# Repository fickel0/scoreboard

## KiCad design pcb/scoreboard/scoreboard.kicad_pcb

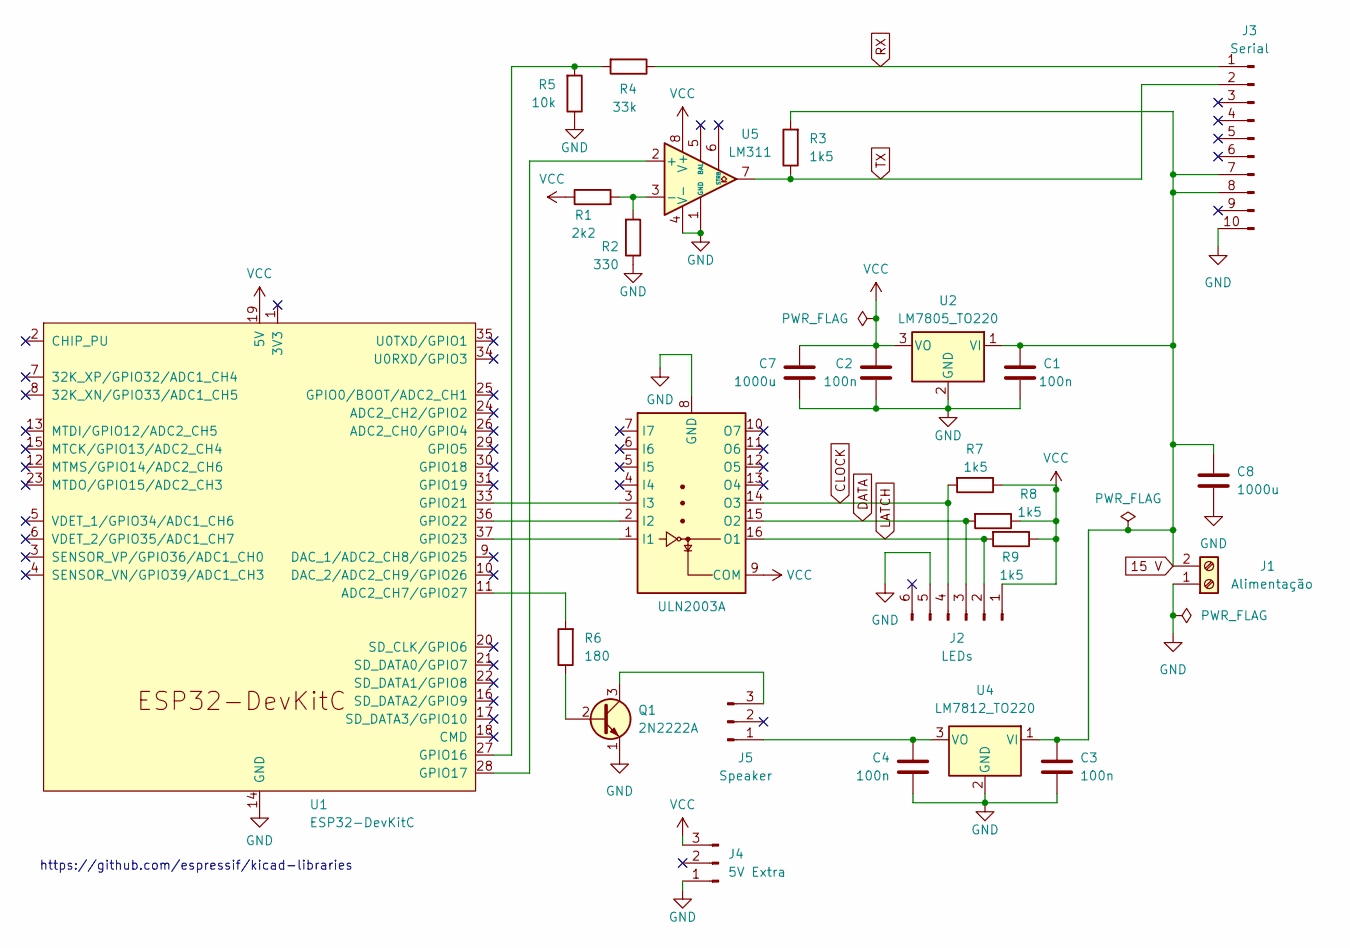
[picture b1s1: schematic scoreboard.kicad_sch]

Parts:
C1, C2, C3, C4: 100n; C_Disc_D5.0mm_W2.5mm_P2.50mm
C7, C8: 1000u; C_Radial_D8.0mm_H11.5mm_P3.50mm
J1: Alimentação; TerminalBlock_Altech_AK300-2_P5.00mm
J2: LEDs; PinHeader_1x06_P2.54mm_Vertical
J3: Serial; PinHeader_2x05_P2.54mm_Vertical
J4: 5V Extra; PinHeader_1x03_P2.54mm_Vertical
J5: Speaker; PinHeader_1x03_P2.54mm_Vertical
Q1: 2N2222A; TO-92_EBC
R1: 2k2; R_Axial_DIN0204_L3.6mm_D1.6mm_P7.62mm_Horizontal
R2: 330; R_Axial_DIN0204_L3.6mm_D1.6mm_P7.62mm_Horizontal
R3, R7: 1k5; R_Axial_DIN0204_L3.6mm_D1.6mm_P7.62mm_Horizontal
R4: 33k; R_Axial_DIN0204_L3.6mm_D1.6mm_P7.62mm_Horizontal
R5: 10k; R_Axial_DIN0204_L3.6mm_D1.6mm_P7.62mm_Horizontal
R6: 180; R_Axial_DIN0204_L3.6mm_D1.6mm_P10.16mm_Horizontal
R8, R9: 1k5; R_Axial_DIN0204_L3.6mm_D1.6mm_P5.08mm_Horizontal
U1: ESP32-DevKitC
U2: LM7805_TO220; TO-220-3_Vertical
U3: ULN2003A; DIP-16_W7.62mm_LongPads
U4: LM7812_TO220; TO-220-3_Vertical
U5: LM311; DIP-8_W7.62mm_LongPads

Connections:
15 V: C1.1, C3.1, C8.1, J1.2, J3.7, J3.8, R3.2, U2.1 (VI), U4.1 (VI)
CLOCK: J2.4, R7.2, U3.14 (O3)
DATA: J2.3, R8.2, U3.15 (O2)
GND: C1.2, C2.2, C3.2, C4.2, C7.2, C8.2, J1.1, J2.5, J3.10, J4.1, Q1.1 (E), R2.1, R5.1, U1.14 (GND), U1.32 (GND), U1.38 (GND), U2.2 (GND), U3.8 (GND), U4.2 (GND), U5.1 (GND), U5.4 (V-)
LATCH: J2.2, R9.2, U3.16 (O1)
unnamed: C4.1, J5.1, U4.3 (VO)
unnamed: J5.3, Q1.3 (C)
unnamed: Q1.2 (B), R6.1
unnamed: R6.2, U1.11 (ADC2_CH7/GPIO27)
unnamed: R4.2, R5.2, U1.27 (GPIO16)
unnamed: U1.28 (GPIO17), U5.2 (+)
unnamed: U1.33 (GPIO21), U3.3 (I3)
unnamed: U1.36 (GPIO22), U3.2 (I2)
unnamed: U1.37 (GPIO23), U3.1 (I1)
unnamed: R1.2, R2.2, U5.3 (-)
RX: J3.1, R4.1
TX: J3.2, R3.1, U5.7
VCC: C2.1, C7.1, J2.1, J4.3, R1.1, R7.1, R8.1, R9.1, U1.19 (5V), U2.3 (VO), U3.9 (COM), U5.8 (V+)

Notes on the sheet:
https://github.com/espressif/kicad-libraries

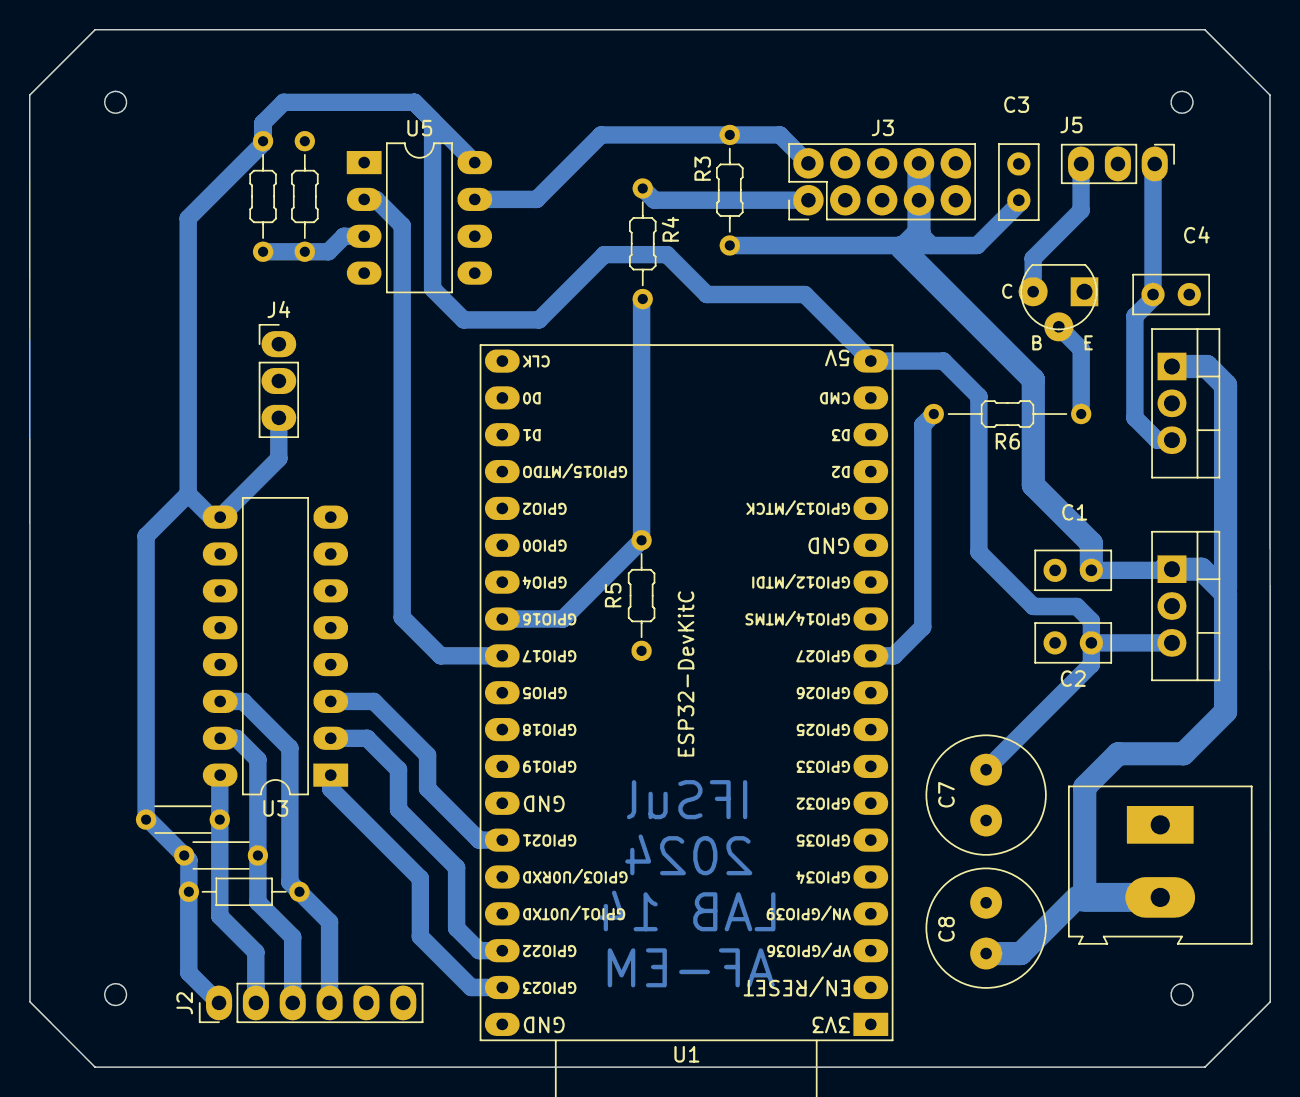
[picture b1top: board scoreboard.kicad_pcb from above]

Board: 2 copper layers, 85.5 x 71.5 mm, 26 parts (0 on the bottom side), 18 nets.

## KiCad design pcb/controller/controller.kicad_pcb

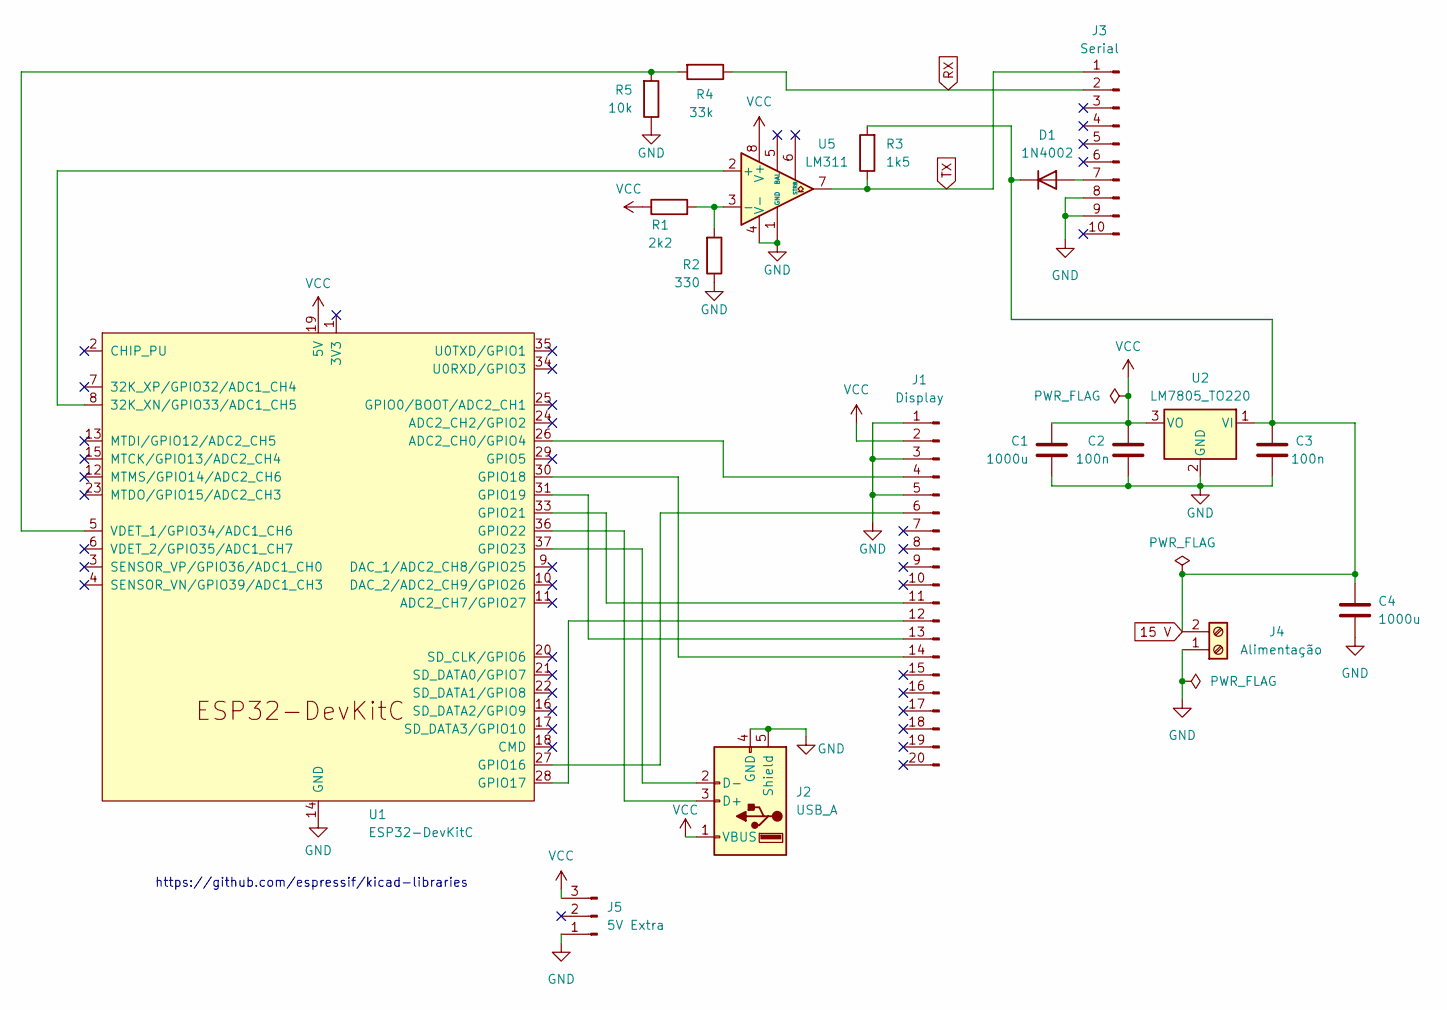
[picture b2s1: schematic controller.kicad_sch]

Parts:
C1, C4: 1000u; C_Radial_D8.0mm_H11.5mm_P3.50mm
C2, C3: 100n; C_Disc_D5.0mm_W2.5mm_P2.50mm
D1: 1N4002; D_DO-41_SOD81_P10.16mm_Horizontal
J1: Display; PinHeader_2x10_P2.54mm_Vertical
J2: USB_A; USB_A_Wuerth_614004134726_Horizontal
J3: Serial; PinHeader_2x05_P2.54mm_Vertical
J4: Alimentação; TerminalBlock_Altech_AK300-2_P5.00mm
J5: 5V Extra; PinHeader_1x03_P2.54mm_Vertical
R1: 2k2; R_Axial_DIN0204_L3.6mm_D1.6mm_P7.62mm_Horizontal
R2: 330; R_Axial_DIN0204_L3.6mm_D1.6mm_P7.62mm_Horizontal
R3: 1k5; R_Axial_DIN0204_L3.6mm_D1.6mm_P7.62mm_Horizontal
R4: 33k; R_Axial_DIN0204_L3.6mm_D1.6mm_P7.62mm_Horizontal
R5: 10k; R_Axial_DIN0204_L3.6mm_D1.6mm_P7.62mm_Horizontal
U1: ESP32-DevKitC
U2: LM7805_TO220; TO-220-3_Vertical
U5: LM311; DIP-8_W7.62mm_LongPads

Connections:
15 V: C3.1, C4.1, D1.1 (K), J4.2, R3.2, U2.1 (VI)
GND: C1.2, C2.2, C3.2, C4.2, J1.1, J1.3, J1.5, J2.4 (GND), J2.5 (Shield), J3.8, J3.9, J4.1, J5.1, R2.1, R5.1, U1.14 (GND), U1.32 (GND), U1.38 (GND), U2.2 (GND), U5.1 (GND), U5.4 (V-)
unnamed: D1.2 (A), J3.7
unnamed: J1.4, U1.26 (ADC2_CH0/GPIO4)
unnamed: J1.6, U1.27 (GPIO16)
unnamed: J1.11, U1.33 (GPIO21)
unnamed: J1.12, U1.28 (GPIO17)
unnamed: J1.13, U1.31 (GPIO19)
unnamed: J1.14, U1.30 (GPIO18)
unnamed: J2.3 (D+), U1.36 (GPIO22)
unnamed: J2.2 (D-), U1.37 (GPIO23)
unnamed: U1.8 (32K_XN/GPIO33/ADC1_CH5), U5.2 (+)
unnamed: R4.2, R5.2, U1.5 (VDET_1/GPIO34/ADC1_CH6)
unnamed: R1.2, R2.2, U5.3 (-)
RX: J3.2, R4.1
TX: J3.1, R3.1, U5.7
VCC: C1.1, C2.1, J1.2, J2.1 (VBUS), J5.3, R1.1, U1.19 (5V), U2.3 (VO), U5.8 (V+)

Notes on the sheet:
https://github.com/espressif/kicad-libraries

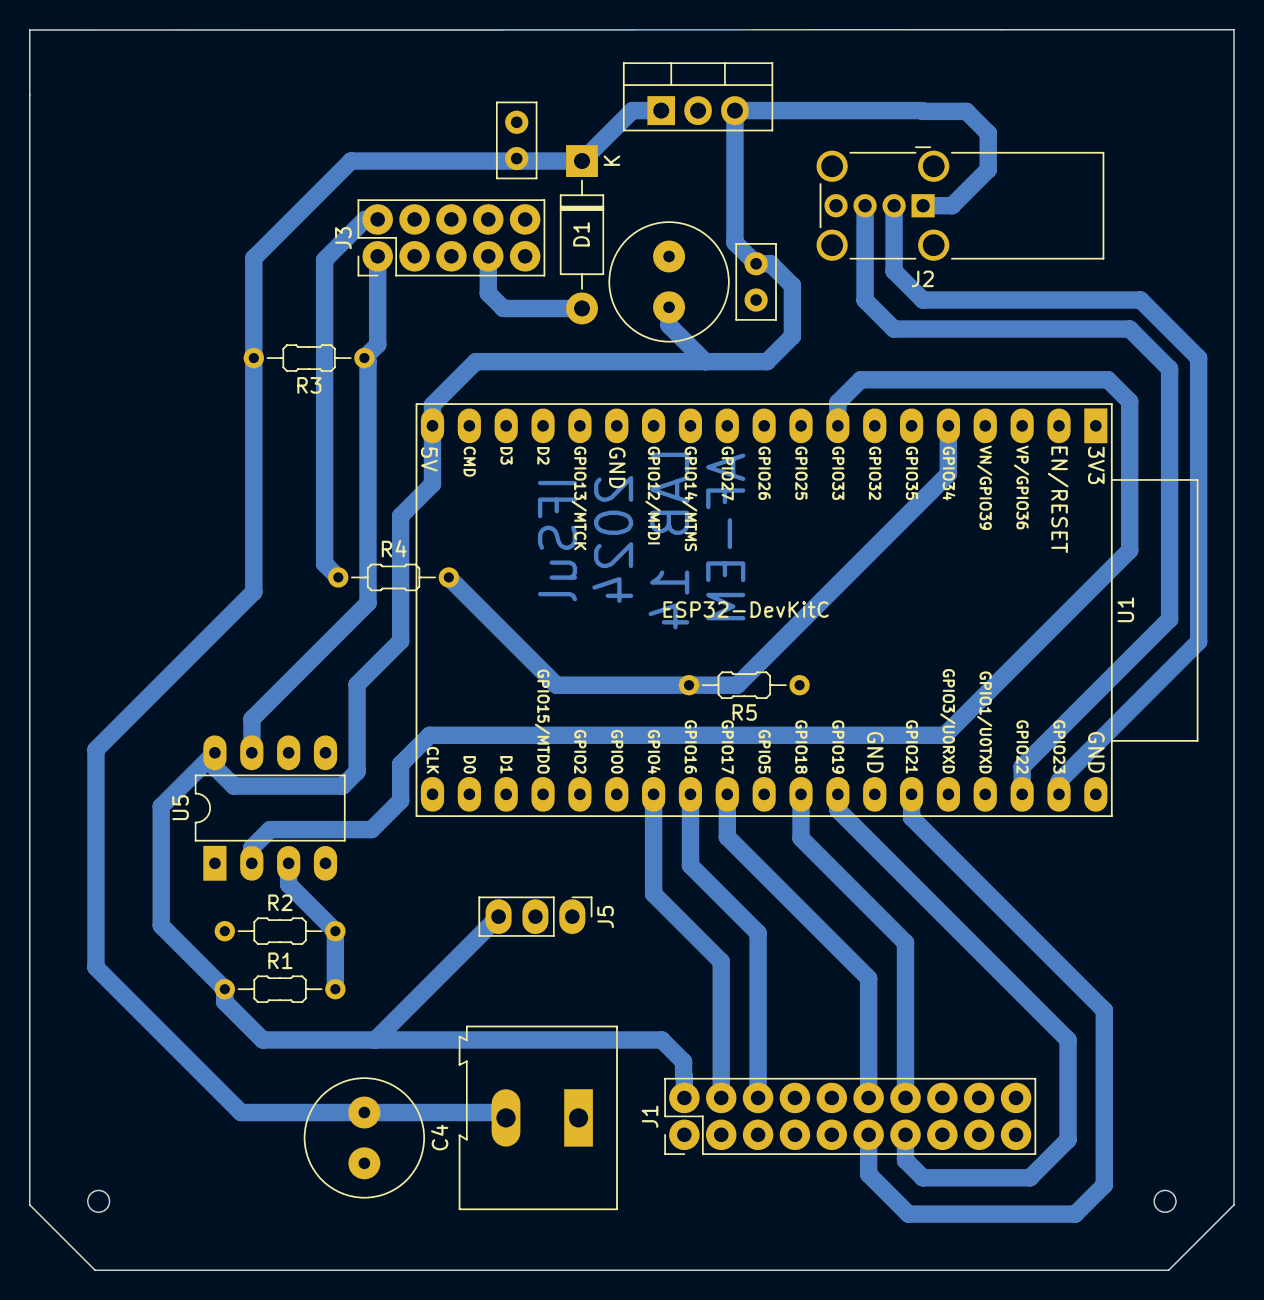
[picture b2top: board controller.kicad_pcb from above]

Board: 2 copper layers, 83.0 x 85.5 mm, 18 parts (0 on the bottom side), 17 nets.

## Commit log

2024-08-30 add new features
2024-08-30 change scoreboard baud rate
